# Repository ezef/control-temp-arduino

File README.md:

Control de temperatura automatico para produccion alimenticia.
desarrollado en Arduino
se incluye diseno de la PCB en kicad y codigo en Arduino

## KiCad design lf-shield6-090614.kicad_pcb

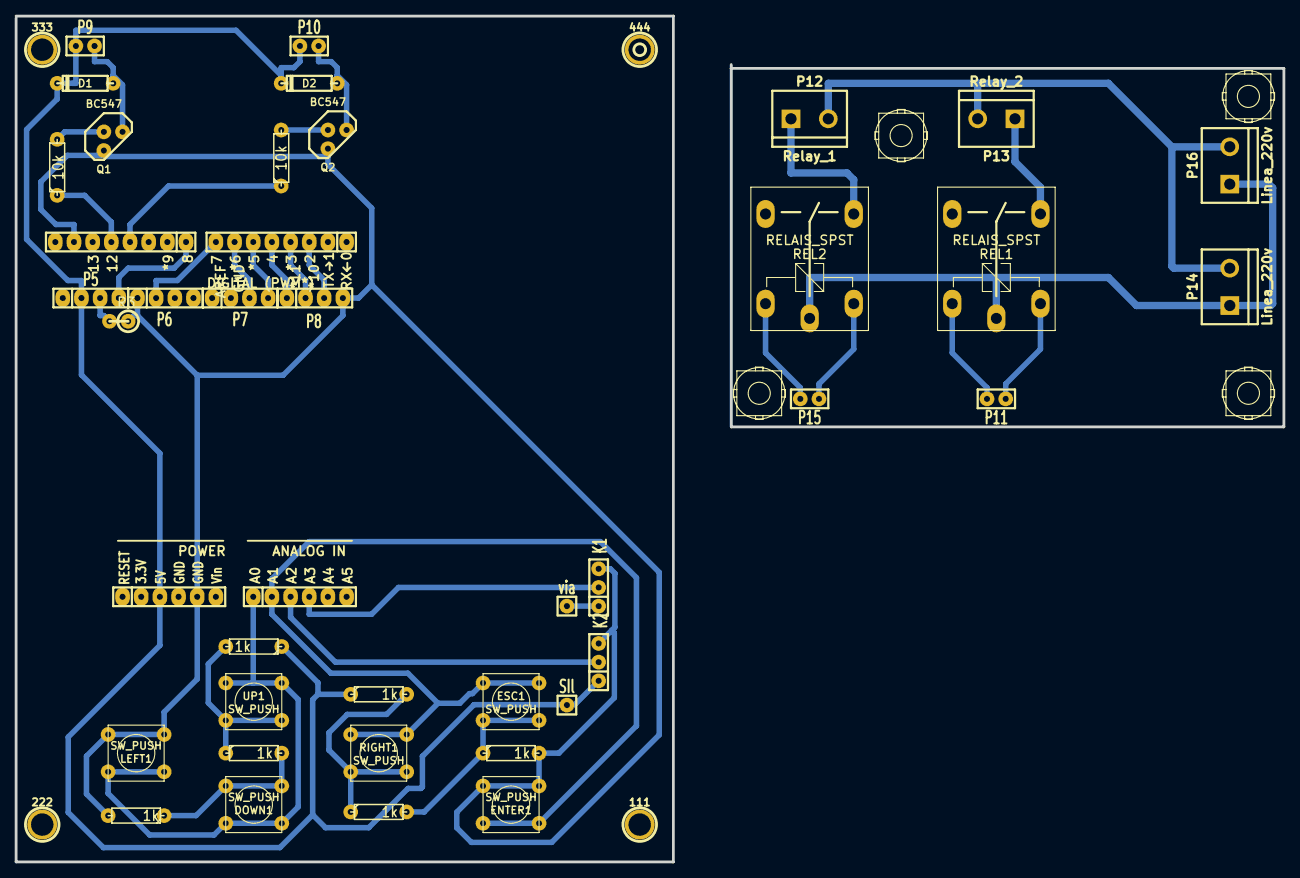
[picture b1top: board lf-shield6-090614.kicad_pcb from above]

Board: 2 copper layers, 172.5 x 115.1 mm, 49 parts (0 on the bottom side), 32 nets.

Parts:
111: 111; 1pin
222: 222; 1pin
333: 333; 1pin
444: 444; 1pin
D1, D2: Diodo_1n4001; D3
DOWN1: SW_PUSH; SW_PUSH_SMALL
ENTER1: SW_PUSH; SW_PUSH_SMALL
ESC1: SW_PUSH; SW_PUSH_SMALL
FORO: HOLE_3mm
FORO#2, FORO#3, FORO#4: HOLE_3mm
K1: LM35_2; SIL-3
K2: LM35_1; SIL-3
LEFT1: SW_PUSH; SW_PUSH_SMALL
P1: IOH; SIL-8
P2: IOL; SIL-8
P3: AD; SIL-6
P4: POWER; SIL-6
P5: CONN_1; SIL-4
P6: CONN_2; SIL-4
P7: CONN_3; SIL-4
P8: CONN_4; SIL-4
P9, P10, P11, P15: Relay; SIL-2
P12: Relay_1; bornier2
P13: Relay_2; bornier2
P14, P16: Linea_220v; bornier2
Q1, Q2: BC547; TO92
R1, R2, R4, R5, R6, R7: 1k; R3
R3: 2.2k; R1
R8, R9: 10k; R3
REL1, REL2: RELAIS_SPST; REL_HJR
RIGHT1: SW_PUSH; SW_PUSH_SMALL
SIl: Val**; SIL-1
UP1: SW_PUSH; SW_PUSH_SMALL
via: Val**; SIL-1

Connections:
+5V: D1.2, D2.2, K1.1, K2.1, P4.3, P5.2, P9.1, P10.1, R1.1, R5.1
/AD0: DOWN1.1, LEFT1.1, P3.1, UP1.1
/AD1: ENTER1.1, ESC1.1, P3.2, RIGHT1.1
/AD2: K2.2, P3.3
/AD3: K1.2, P3.4
/IO2: P2.3, P8.3
/IO3: P2.4, P8.2
/IO4: P2.5, P8.1
/IO5: P2.6, P7.4
/IO6: P2.7, P7.3
/IO7: P2.8, P6.2
/IO8: P1.1, P5.4
/MISO: P1.5, R8.1
/MOSI: P1.4, R9.1
GND: ENTER1.2, K1.3, K2.3, LEFT1.2, P1.7, P4.5, P6.1, P8.4, Q1.3, Q2.3, R2.2, R3.1, R7.2
unnamed: R5.2, R6.1, RIGHT1.2
unnamed: ESC1.2, R6.2, R7.1
unnamed: D2.1, P10.2, Q2.1
unnamed: Q2.2, R9.2
unnamed: R1.2, R4.1, UP1.2
unnamed: DOWN1.2, R2.1, R4.2
unnamed: P5.3, R3.2
unnamed: P12.2, P13.2, P14.2, P16.2
unnamed: P15.1, REL2.5
unnamed: P11.2, REL1.4
unnamed: P14.1, P16.1, REL1.2, REL2.2
unnamed: P13.1, REL1.3
unnamed: P11.1, REL1.5
unnamed: P12.1, REL2.3
unnamed: Q1.2, R8.2
unnamed: D1.1, P9.2, Q1.1
unnamed: P15.2, REL2.4

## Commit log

2015-02-19 erste commit
2015-02-19 commit 2
2015-02-23 delets
2015-02-23 delete
2016-10-24 added a second control block with DS18b20 sensor
2016-10-25 correction
